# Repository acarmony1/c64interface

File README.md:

# c64interface
 Commdore 64 Userport Interface
 
 I have been working on interface for the Commodore 64's userport. This interface allows user to use the C64 like you would any microcontroller. At this time it only turns on and off 8 pins, pins PB0-7.

There are many things that can be done with the C64's userport, which I will be looking into adding in the future. For now take a look at acarmony1/c64interface: Commodore 64 Userport Interface (github.com) for more information, schematics, and a demo program.

https://carmony.xyz/10-commodore/commodore-64-projects/9-c64-userport-interface.html

https://carmony.xyz/

Use the interface.prg as a demo to use this interface. Take note if the interface is powered up, and the C64 is off all ports are turned ON. This was the design I used from the Projects for the C64 book. In future versions, I may impletment a 'fail safe', where if no power from the C64 the unit shuts down.

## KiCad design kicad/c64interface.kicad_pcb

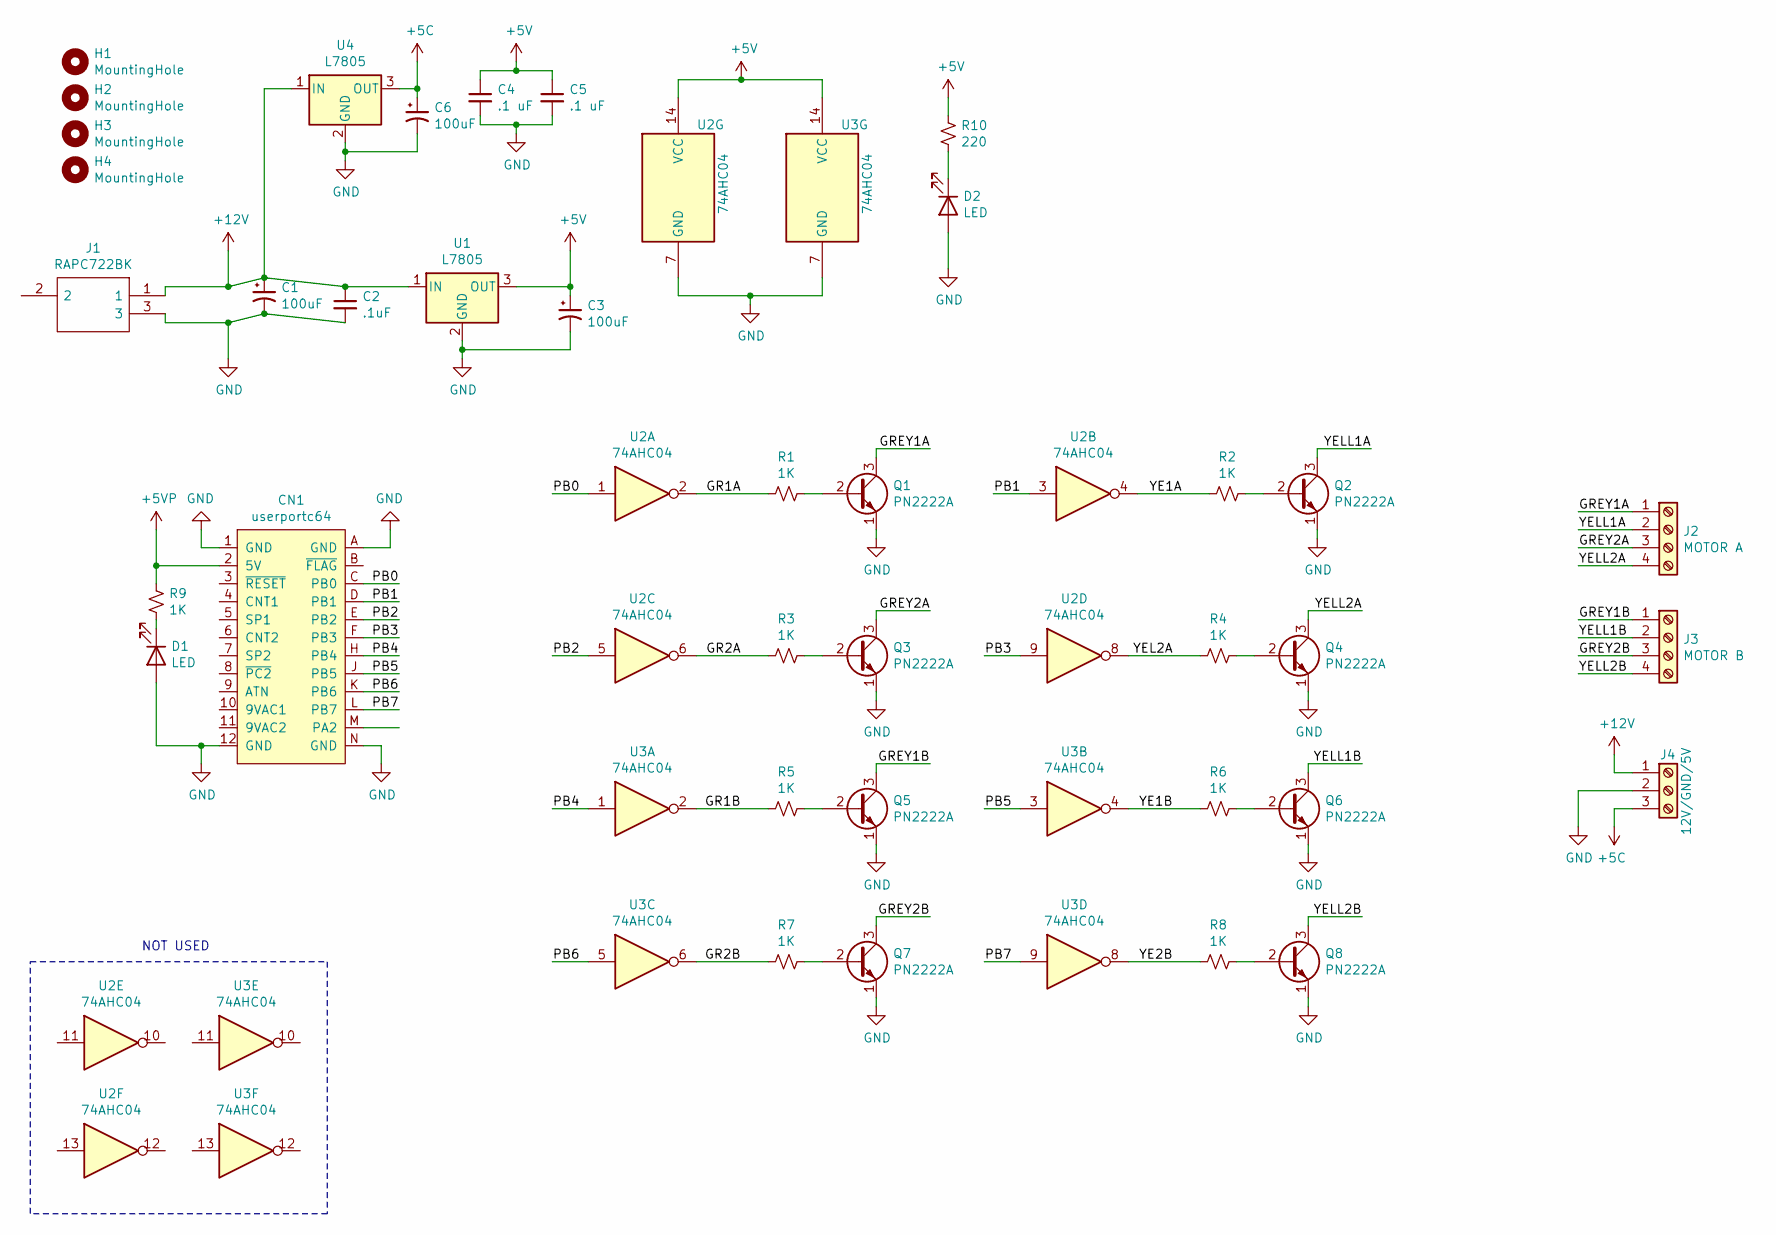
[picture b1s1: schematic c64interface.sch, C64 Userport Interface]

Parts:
C1, C3, C6: 100uF; CP_Radial_D5.0mm_P2.50mm
C2: .1uF; C_Disc_D3.8mm_W2.6mm_P2.50mm
C4, C5: .1 uF; C_Disc_D3.8mm_W2.6mm_P2.50mm
CN1: userportc64; PinHeader_2x12_P2.54mm_Horizontal
D1, D2: LED; LED_D3.0mm
H1, H2, H3, H4: MountingHole; MountingHole_3.2mm_M3_DIN965_Pad
J1: RAPC722BK; Mouser Part Number 502-RAPC722BK
J2: MOTOR A; TerminalBlock_TE_282834-4_1x04_P2.54mm_Horizontal
J3: MOTOR B; TerminalBlock_TE_282834-4_1x04_P2.54mm_Horizontal
J4: 12V/GND/5V; TerminalBlock_TE_282834-3_1x03_P2.54mm_Horizontal
Q1, Q2, Q3, Q4, Q5, Q6, Q7, Q8: PN2222A; TO-92_Inline
R1, R2, R3, R4, R5, R6, R7, R8, R9: 1K; R_Axial_DIN0207_L6.3mm_D2.5mm_P10.16mm_Horizontal
R10: 220; R_Axial_DIN0207_L6.3mm_D2.5mm_P10.16mm_Horizontal
U1, U4: L7805; TO-220-3_Vertical
U2, U3: 74AHC04; DIP-14_W7.62mm_Socket_LongPads

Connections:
+5C: C6.1, J4.3, U4.3 (OUT)
+5V: C3.1, C4.1, C5.1, R10.2, U1.3 (OUT), U2.14 (VCC), U3.14 (VCC)
+5VP: CN1.2 (5V), R9.2
+12V: C1.1, C2.1, J1.1, J4.1, U1.1 (IN), U4.1 (IN)
/GR1A: R1.2, U2.2
/GR1B: R5.2, U3.2
/GR2A: R3.2, U2.6
/GR2B: R7.2, U3.6
/GREY1A: J2.1, Q1.3 (C)
/GREY1B: J3.1, Q5.3 (C)
/GREY2A: J2.3, Q3.3 (C)
/GREY2B: J3.3, Q7.3 (C)
/PB0: CN1.C (PB0), U2.1
/PB1: CN1.D (PB1), U2.3
/PB2: CN1.E (PB2), U2.5
/PB3: CN1.F (PB3), U2.9
/PB4: CN1.H (PB4), U3.1
/PB5: CN1.J (PB5), U3.3
/PB6: CN1.K (PB6), U3.5
/PB7: CN1.L (PB7), U3.9
/YE1A: R2.2, U2.4
/YE1B: R6.2, U3.4
/YE2B: R8.2, U3.8
/YEL2A: R4.2, U2.8
/YELL1A: J2.2, Q2.3 (C)
/YELL1B: J3.2, Q6.3 (C)
/YELL2A: J2.4, Q4.3 (C)
/YELL2B: J3.4, Q8.3 (C)
GND: C1.2, C2.2, C3.2, C4.2, C5.2, C6.2, CN1.1 (GND), CN1.12 (GND), CN1.A (GND), CN1.N (GND), D1.2 (A), D2.2 (A), J1.3, J4.2, Q1.1 (E), Q2.1 (E), Q3.1 (E), Q4.1 (E), Q5.1 (E), Q6.1 (E), Q7.1 (E), Q8.1 (E), U1.2 (GND), U2.7 (GND), U3.7 (GND), U4.2 (GND)
unnamed: D1.1 (K), R9.1
unnamed: D2.1 (K), R10.1
unnamed: Q1.2 (B), R1.1
unnamed: Q2.2 (B), R2.1
unnamed: Q3.2 (B), R3.1
unnamed: Q4.2 (B), R4.1
unnamed: Q5.2 (B), R5.1
unnamed: Q6.2 (B), R6.1
unnamed: Q7.2 (B), R7.1
unnamed: Q8.2 (B), R8.1

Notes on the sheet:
NOT USED

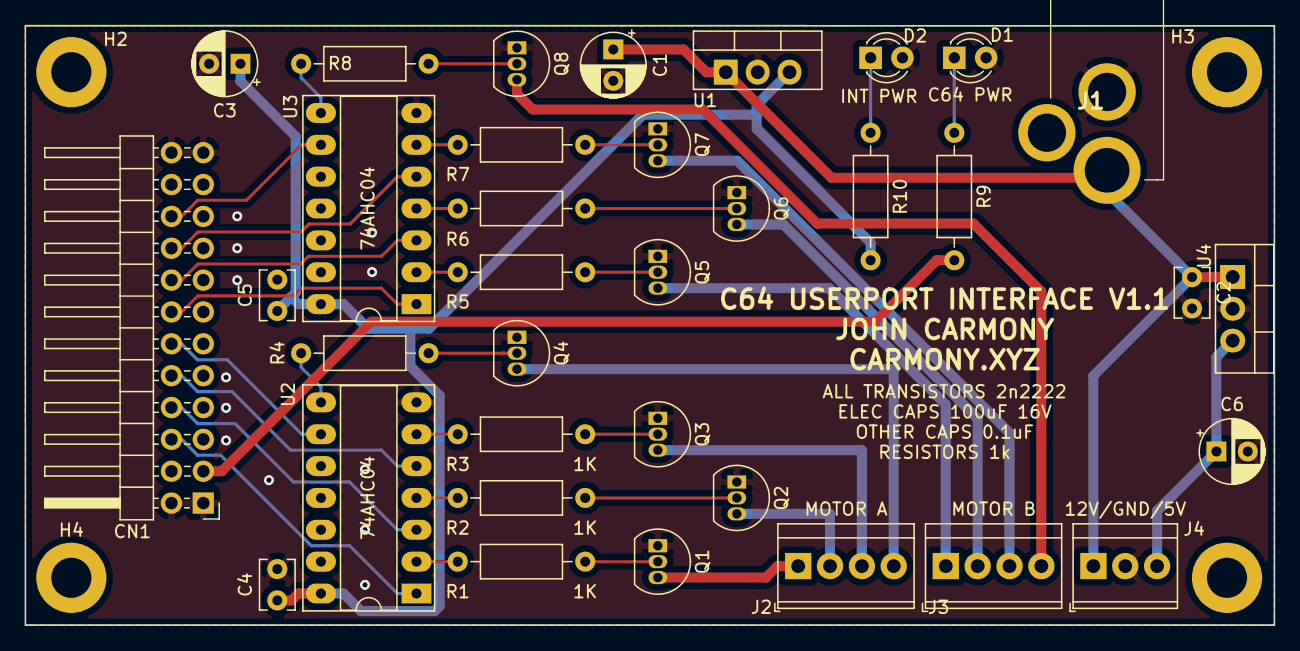
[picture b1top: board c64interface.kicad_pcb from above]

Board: 2 copper layers, 99.6 x 47.8 mm, 39 parts (0 on the bottom side), 39 nets.

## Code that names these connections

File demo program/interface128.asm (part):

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	
pboutput	= %11111111			; 255	(userport output)	
pboff		= %00000000			; 0 	(all off)	
pb0			= %00000001			; 1		(port0)
pb1			= %00000010			; 2 	(port1)
pb2			= %00000100			; 4		(port2)
pb3			= %00001000			; 8		(port3)
pb4			= %00010000			; 16	(port4)
pb5			= %00100000			; 32	(port5)
pb6			= %01000000			; 64	(port6)
pb7			= %10000000			; 128	(port7)
pball		= %11111111			; 255 	(all on)

zp1			= $fb				; zero page 1 location
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	;	MENU COMMANDS (removed JSR's for speed)
	;

zero		lda #pb0			; switch the port on/off							
			jmp switchport
			
one			lda #pb1			; switch the port on/off							
			jmp switchport
			
two			lda #pb2			; switch the port on/off			
			jmp switchport
			
three		lda #pb3			; switch the port on/off			
			jmp switchport
			
four		lda #pb4			; switch the port on/off			
			jmp switchport
			
five		lda #pb5			; switch the port on/off			
			jmp switchport
			
six			lda #pb6			; switch the port on/off			
			jmp switchport

seven		lda #pb7			; switch the port on/off			
			jmp switchport
			
allon		lda #pball			; load all on
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+			lda #off			; reset flag back to OFF
			sta flag			; store it	
			
			lda #pb0 			; load port 0	; check to see if it's already on
			bit portloc
			beq +				; it is, jump ahead
			
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				
			jsr rvsont			; set rvs indicator to 'on'
						
+			lda #pb1			; load port 1	; check to see if it's already on
			bit portloc
			beq +				; it is, jump ahead
			
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			
			jsr rvsont			; set rvs indicator to 'on'
			
+			lda #pb2			; load port 2	; check to see if it's already on
			bit portloc
			beq +				; it is, jump ahead
			
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				
			jsr rvsont			; set rvs indicator to 'on'
			
+			lda #pb3			; load port 3	; check to see if it's already on
			bit portloc
			beq +				; it is, jump ahead
			
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			
			jsr rvsont			; set rvs indicator to 'on'

+			lda #pb4			; load port 4	; check to see if it's already on
			bit portloc
			beq +				; it is, jump ahead
			
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			
			jsr rvsont			; set rvs indicator to 'on'
			
+			lda #pb5			; load port 5	; check to see if it's already on
			bit portloc
			beq +				; it is, jump ahead
				
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			
			jsr rvsont			; set rvs indicator to 'on'
			
+			lda #pb6			; load port 6	; check to see if it's already on
			bit portloc
			beq +				; it is, jump ahead
			
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						
			jsr rvsont			; set rvs indicator to 'on'
			
+			lda #pb7			; load port 7	; check to see if it's already on
			bit portloc
			beq +				; it is, jump ahead
			
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		;	SCAN PORTS FOR 'OFF' STATUS
		;

+			lda #pb0			; port 0	; check to see if it's alread off
			bit portloc 
			bne +				; it is, jump ahead
			
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			
			jsr rvsofft			; set rvs indicator to 'off'
			
+			lda #pb1			; load port 1	; check to see if it's already off
			bit portloc
			bne +				; it is, jump ahead
			
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			
			jsr rvsofft			; set rvs indicator to 'off'
			
+			lda #pb2			; load port 2	; check to see if it's already off
			bit portloc
			bne +				; it is, jump ahead
			
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			
			jsr rvsofft			; set rvs indicator to 'off'
			
+			lda #pb3			; load port 3	; check to see if it's already off
			bit portloc
			bne +				; it is, jump ahead
			
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			
			jsr rvsofft			; set rvs indicator to 'off'

+			lda #pb4			; load port 4	; check to see if it's already off
			bit portloc
			bne +				; it is, jump ahead
			
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			
			jsr rvsofft			; set rvs off indicator
			
+			lda #pb5			; load port 5	; check to see if it's already off
			bit portloc
			bne +				; set loc port 5	
			
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			
			jsr rvsofft			; set rvs indicator to 'off'
			
+			lda #pb6			; load port 6	; check to see if it's already off
			bit portloc
			bne +				; it is, jump head
			
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			
			jsr rvsofft			; set rvs off indicator
			
+			lda #pb7			; port 7	; check to see if it's already off
			bit portloc
			bne +				; it is, jump ahead
			
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
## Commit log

2021-06-26 V1.3, C128, ISR optimize
    Added C128 version, ISR optimization. Cosmetic changes
